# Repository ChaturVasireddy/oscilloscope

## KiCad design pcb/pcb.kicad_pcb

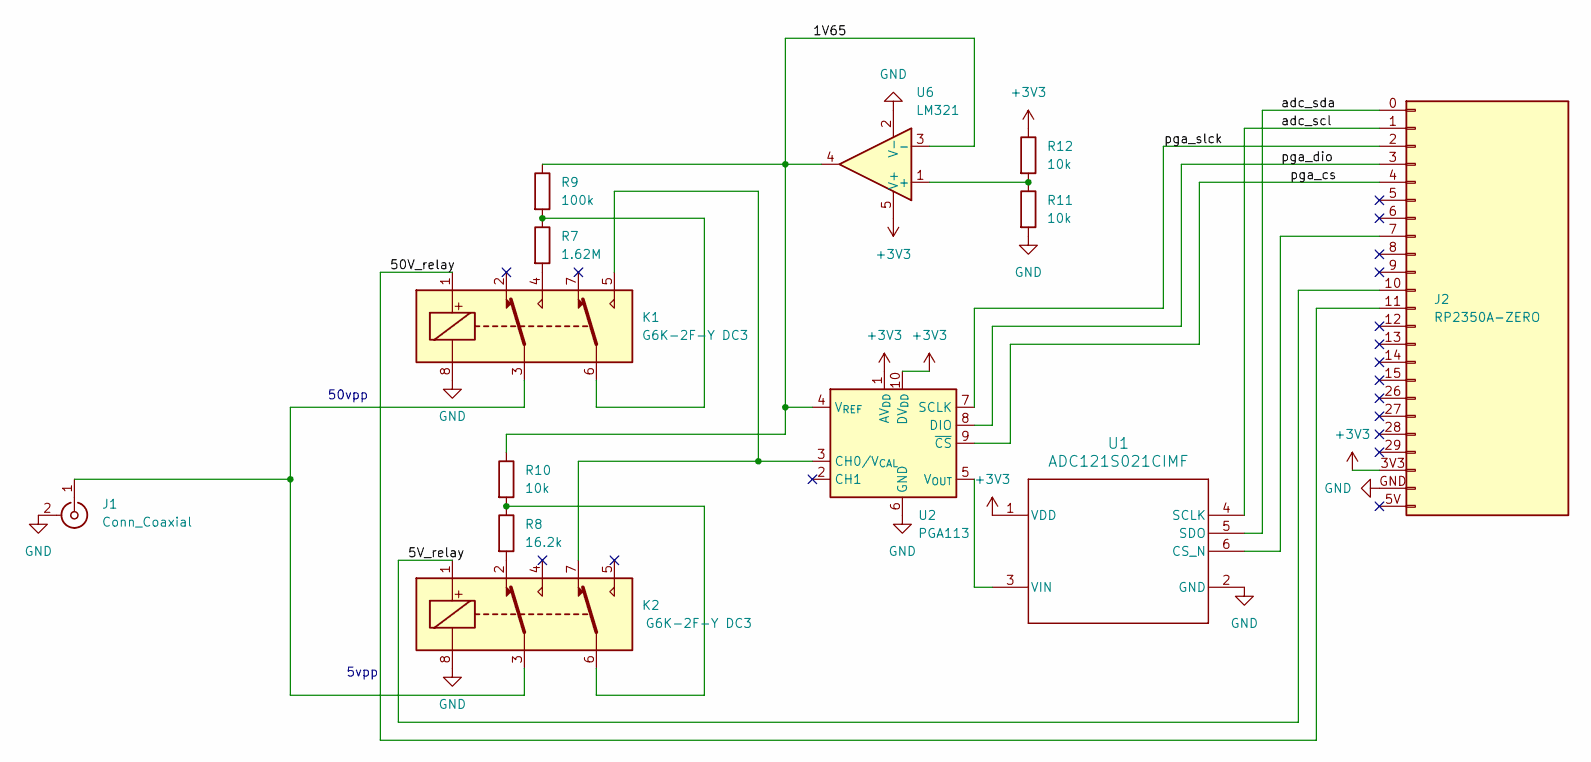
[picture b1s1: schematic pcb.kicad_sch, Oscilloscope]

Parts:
J1: Conn_Coaxial; BNC-connector
J2: RP2350A-ZERO
K1, K2: G6K-2F-Y DC3; Relay_DPDT_Omron_G6K-2F-Y
R7: 1.62M; R_2010_5025Metric_Pad1.40x2.65mm_HandSolder
R8: 16.2k; R_0603_1608Metric_Pad0.98x0.95mm_HandSolder
R9: 100k; R_0805_2012Metric_Pad1.20x1.40mm_HandSolder
R10, R11, R12: 10k; R_0603_1608Metric_Pad0.98x0.95mm_HandSolder
U1: ADC121S021CIMF; SOT-23-6_Handsoldering
U2: PGA113; TSSOP-10_3x3mm_P0.5mm
U6: LM321; SOT-23-5_HandSoldering

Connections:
+3V3: J2.3V3 (Pin_21), R12.1, U1.1 (VDD), U2.1 (AV_{DD}), U2.10 (DV_{DD}), U6.5 (V+)
/1V65: R9.1, R10.1, U2.4 (V_{REF}), U6.3 (-), U6.4
/5V_relay: J2.10 (Pin_11), K2.1
/50V_relay: J2.11 (Pin_12), K1.1
/adc_scl: J2.1 (Pin_2), U1.4 (SCLK)
/adc_sda: J2.0 (Pin_1), U1.5 (SDO)
/pga_cs: J2.4 (Pin_5), U2.9 (~CS)
/pga_dio: J2.3 (Pin_4), U2.8 (DIO)
/pga_slck: J2.2 (Pin_3), U2.7 (SCLK)
GND: J1.2 (Ext), J2.GND (Pin_22), K1.8, K2.8, R11.2, U1.2 (GND), U2.6 (GND), U6.2 (V-)
unnamed: J1.1 (In), K1.3, K2.3
unnamed: J2.7 (Pin_8), U1.6 (CS_N)
unnamed: K1.4, R7.2
unnamed: K1.6, R7.1, R9.2
unnamed: K2.2, R8.2
unnamed: K2.6, R8.1, R10.2
unnamed: U1.3 (VIN), U2.5 (V_{OUT})
unnamed: K1.5, K2.7, U2.3 (CH0/V_{CAL})
unnamed: R11.1, R12.2, U6.1 (+)

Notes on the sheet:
5vpp
50vpp

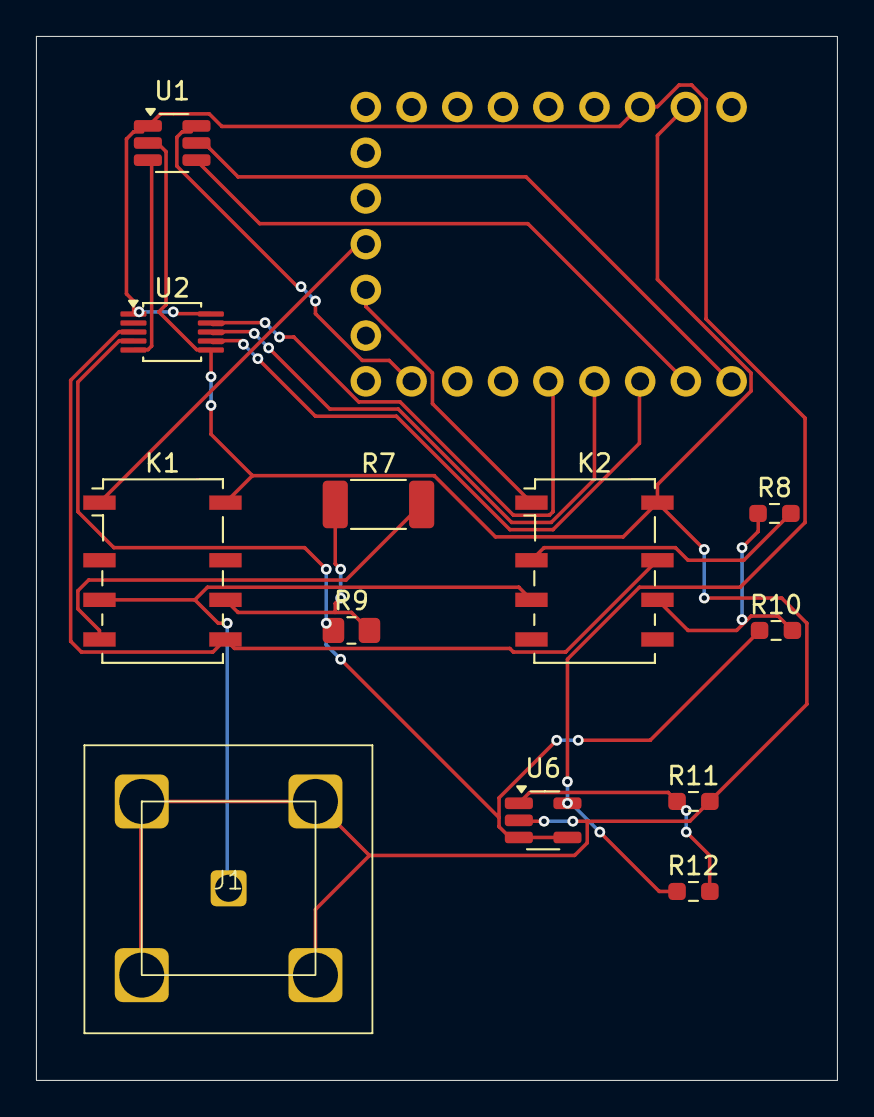
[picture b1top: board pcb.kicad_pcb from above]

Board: 2 copper layers, 44.5 x 58.0 mm, 13 parts (0 on the bottom side), 19 nets.
